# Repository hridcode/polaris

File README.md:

# Polaris

Polaris is a portable cyberdeck for everyday use. It does not use a Raspberry Pi or other SBC, but rather an RP2354B with extra PSRAM! It is meant for having an on-the-go device to use for everyday tasks.

## Features

- RP2354B SoC
- 520KB SRAM + 2MB PSRAM
- 2MB flash memory
- 5x10 thumb-size keyboard
- SD card slot
- USB-C port
- Battery charging with power path (IP2306)
- Audio output through speaker (MAX98357A)
- GPIO access
- Expansion port for apps

## Pictures

|Schematic|PCB|Case|
|---|---|---|
||||

## BOM

|Part|Quantity|Cost|Link|
|---|---|---|---|
|0402 20pF capacitor|2|$0.016|[LCSC](https://www.lcsc.com/product-detail/C1554.html)|
|0402 0.1uF capacitor|13|$0.072|[LCSC](https://www.lcsc.com/product-detail/C1525.html)|
|0402 4.7uF capacitor|3|$0.070|[LCSC](https://www.lcsc.com/product-detail/C23733.html)|
|0402 10uF capacitor|7|$0.181|[LCSC](https://www.lcsc.com/product-detail/C15525.html)|
|0603 22uF capacitor|3|$0.094|[LCSC](https://www.lcsc.com/product-detail/C59461.html)|
|0402 1uH inductor|1|$0.035|[LCSC](https://www.lcsc.com/product-detail/C84468.html)|
|0402 3.3uH inductor|1|$0.076|[LCSC](https://www.lcsc.com/product-detail/C84474.html)|
|0603 2Ω resistor|2|$0.006|[LCSC](https://www.lcsc.com/product-detail/C22977.html)|
|0603 27Ω resistor|2|$0.007|[LCSC](https://www.lcsc.com/product-detail/C25190.html)|
|0402 33Ω resistor|1|$0.008|[LCSC](https://www.lcsc.com/product-detail/C25105.html)|
|0603 220Ω resistor|8|$0.028|[LCSC](https://www.lcsc.com/product-detail/C22962.html)|
|0402 1KΩ resistor|2|$0.008|[LCSC](https://www.lcsc.com/product-detail/C11702.html)|
|0402 4.7KΩ resistor|2|$0.010|[LCSC](https://www.lcsc.com/product-detail/C25905.html)|
|0402 5.1KΩ resistor|2|$0.005|[LCSC](https://www.lcsc.com/product-detail/C25905.html)|
|0402 10KΩ resistor|5|$0.024|[LCSC](https://www.lcsc.com/product-detail/C25905.html)|
|BAW56S quad-diode package|12|$1.778|[LCSC](https://www.lcsc.com/product-detail/C426776.html)|
|USB-C receptacle, 14 pin|1|$0.172|[LCSC](https://www.lcsc.com/product-detail/C165948.html)|
|HDMI-A receptacle|1|$0.245|[LCSC](https://www.lcsc.com/product-detail/C720616.html)|
|microSD card receptacle|1|$0.061|[LCSC](https://www.lcsc.com/product-detail/C7529389.html)|
|3.9x2.9mm tactile switch|48|$1.627|[LCSC](https://www.lcsc.com/product-detail/C557591.html)|
|SPST rocker switch|1|$0.156|[LCSC](https://www.lcsc.com/product-detail/C6917318.html)|
|MAX98357A sound IC|1|$1.328|[LCSC](https://www.lcsc.com/product-detail/C910544.html)|
|Speaker|1|$0.995|[AliExpress](https://www.aliexpress.us/item/3256810283962305.html)|
|IP5306 battery charging IC|1|$0.299|[LCSC](https://www.lcsc.com/product-detail/C181692.html)|
|104050 3.7V 2500mAh LiPo battery|1|$8.790|[AliExpress](https://www.aliexpress.us/item/3256808739822835.html)|
|RP2354B|1|$1.551|[LCSC](https://www.lcsc.com/product-detail/C39843328.html)|
|XC6206P332MR 3.3V power regulator|1|$0.147|[LCSC](https://www.lcsc.com/product-detail/C5446.html)|
|APS1604M-3SQRx-SN 2MB PSRAM|1|$2.586|[LCSC](https://www.lcsc.com/product-detail/C18214056.html)|
|DS3231MZ real-time clock|1|$3.298|[LCSC](https://www.lcsc.com/product-detail/C107410.html)|
|CR1220 battery holder|1|$0.196|[LCSC](https://www.lcsc.com/product-detail/C964723.html)|
|12MHz 20pF crystal oscillator|1|$0.096|[LCSC](https://www.lcsc.com/product-detail/C9002.html)|
|1x5 right-angled pin header|1|$0.075|[LCSC](https://www.lcsc.com/product-detail/C54876734.html)|
|2x7 right-angled pin header|1|$0.328|[LCSC](https://www.lcsc.com/product-detail/C46061748.html)|
|5" 800x480 LCD display|1|$34.990|[Waveshare](https://www.waveshare.com/product/displays/lcd-oled/lcd-oled-1/5inch-hdmi-lcd.htm)|
|Total||$59.358||

## Notes

The firmware is still being developed. There will be more applications once the device is built.

Check `/firmware/src/main.cpp` for libraries/dependencies required to run the firmware.

PNP assembly files are provided if you'd want to get this assembled. The parts list is optimized for JLCPCB's Economic PCB assembly.

Have fun!

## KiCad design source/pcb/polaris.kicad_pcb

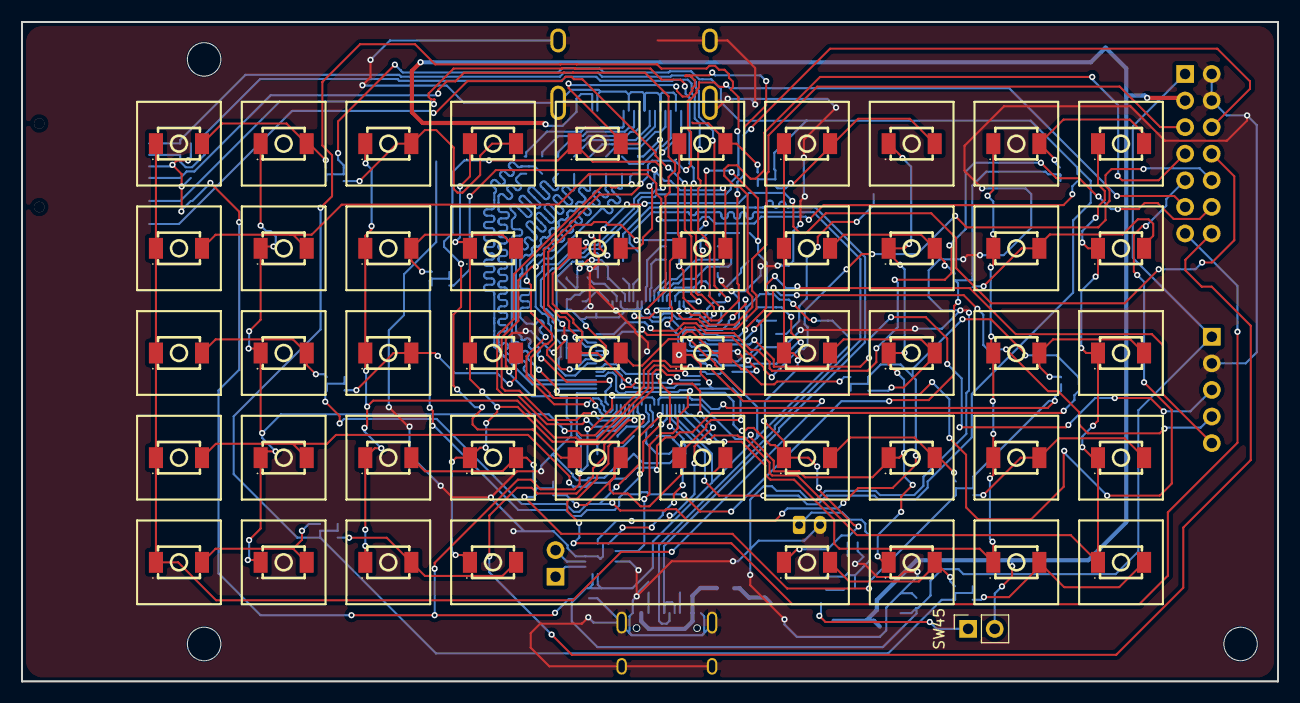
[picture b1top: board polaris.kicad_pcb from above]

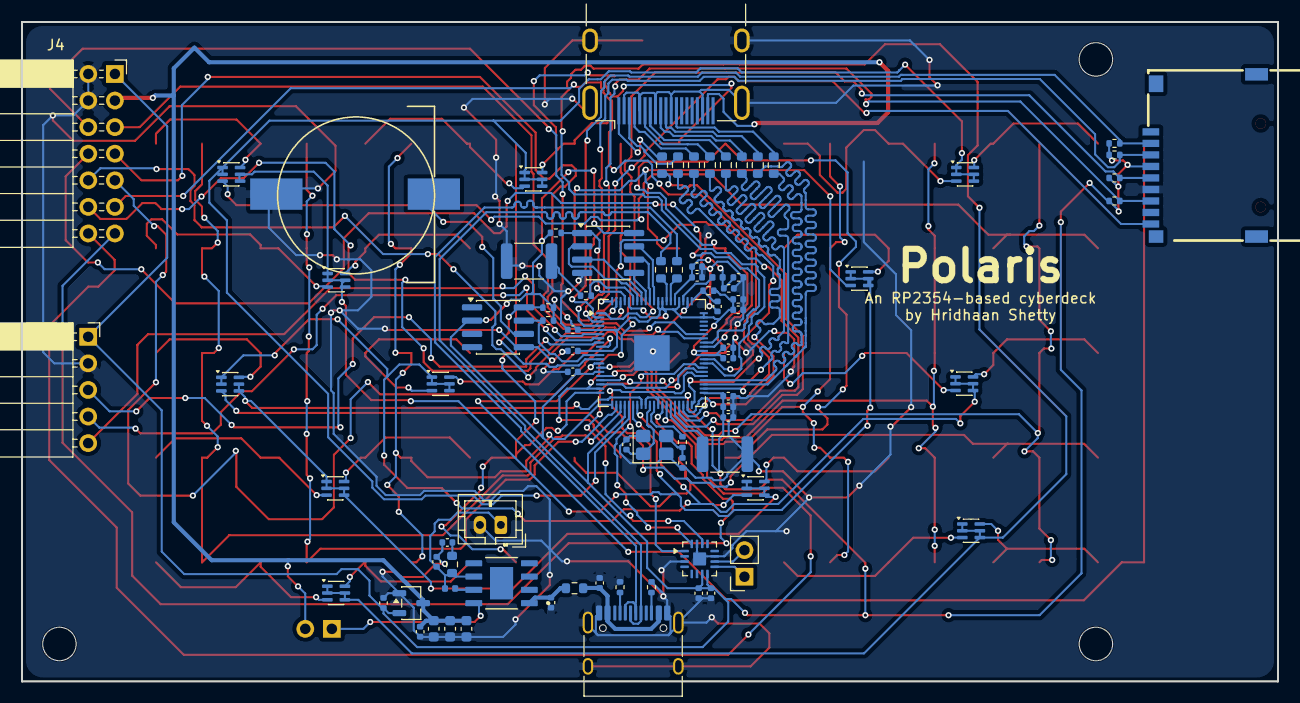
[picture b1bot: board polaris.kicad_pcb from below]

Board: 2 copper layers, 120.0 x 63.0 mm, 135 parts (83 on the bottom side), 111 nets.

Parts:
BT1: Battery_Cell; CR1220_Battery_Holder
C1, C2, C3: 4.7uF; C_0402_1005Metric
C4, C5: 20pF; C_0402_1005Metric
C6, C7, C8, C12, C13, C14, C15, C16, C17, C18, C19, C20, C28: 0.1uF; C_0402_1005Metric
C9, C10, C23, C24, C25, C26, C27: 10uF; C_0402_1005Metric
C11, C21, C22: 22uF; C_0603_1608Metric
D1, D2, D3, D4, D5, D6, D7, D8, D9, D10, D11, D12: BAW56S; SOT-363_SC-70-6
H1, H2, H3: MountingHole; MountingHole_3.2mm_M3
J1: USB_C_Receptacle_USB2.0_14P; USB_C_Receptacle_HRO_TYPE-C-31-M-12
J2: HDMI_A; HDMI_A_Molex_208658-1001_Horizontal
J3: Conn_01x05; PinSocket_1x05_P2.54mm_Horizontal
J4: Conn_02x07_Odd_Even; PinSocket_2x07_P2.54mm_Horizontal
J5: Micro_SD_Card_Det1; TF-SMD_TF-CARD-H1.8
J6: Conn_01x02; JST_PH_B2B-PH-K_1x02_P2.00mm_Vertical
L1: 3.3uH; L_0402_1005Metric
L2: 1uH; L_0402_1005Metric
LS1: Speaker; PinSocket_1x02_P2.54mm_Vertical
R1, R2: 5.1K; R_0402_1005Metric
R3, R4: 27; R_0603_1608Metric
R5: 33; R_0402_1005Metric
R6, R7: 1K; R_0402_1005Metric
R8, R9: 2; R_0603_1608Metric
R10, R11, R12, R13, R14, R15, R16, R17: 220; R_0603_1608Metric
R18, R19: 4.7K; R_0402_1005Metric
R20, R21, R22, R23, R24: 10K; R_0402_1005Metric
SW1, SW2, SW3, SW4, SW5, SW6, SW7, SW8, SW9, SW10, SW11, SW12, SW13, SW14, SW15, SW16, SW17, SW18, SW19, SW20, SW21, SW22, SW23, SW24, SW25, SW26, SW27, SW28, SW29, SW30, SW31, SW32, SW33, SW34, SW35, SW36, SW37, SW38, SW39, SW40, SW41, SW42, SW43, SW44, SW47, SW48, SW49, SW50: SW_Push; SW-SMD_L4.0-W3.0-LS5.0
SW45: SW_SPST; PinSocket_1x02_P2.54mm_Vertical
SW51, SW52: SW_Push; R_1812_4532Metric
U1: MAX98357A; TQFN-16-1EP_3x3mm_P0.5mm_EP1.23x1.23mm
U2: IP5306; eSOP-8
U3: RP2354B; QFN-80-1EP_10x10mm_P0.4mm_EP3.4x3.4mm
U4: XC6206PxxxMR; SOT-23-3
U5: APS1604M-3SQRx-SN; SOIC-8_3.9x4.9mm_P1.27mm
U6: DS3231MZ; SOIC-8_3.9x4.9mm_P1.27mm
Y1: Crystal_GND24; Crystal_SMD_3225-4Pin_3.2x2.5mm

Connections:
+1V1: C2.1, C6.1, C7.1, C8.1, L1.1, U3.65 (VREG_FB)
+3V3: C1.1, C12.1, C13.1, C14.1, C15.1, C16.1, C17.1, C18.1, C19.1, C20.1, C24.1, C27.1, C28.1, J3.1, J4.1, J5.4 (VDD), R5.1, R18.2, R19.1, R20.2, R21.2, R22.2, R23.2, R24.2, U1.7 (VDD), U1.8 (VDD), U3.5 (IOVDD), U3.10 (DVDD), U3.15 (IOVDD), U3.24 (IOVDD), U3.29 (IOVDD), U3.32 (DVDD), U3.41 (IOVDD), U3.50 (IOVDD), U3.51 (DVDD), U3.59 (ADC_AVDD), U3.60 (IOVDD), U3.64 (VREG_VIN), U3.68 (USB_OTP_VDD), U3.69 (QSPI_IOVDD), U3.76 (IOVDD), U4.2 (VO), U5.8 (VDD), U6.2 (VCC)
+5V: C11.1, C21.1, C22.1, C23.1, J2.18 (+5V), J4.3, SW45.2 (B), U4.3 (VI)
ADC0: J4.11, U3.49 (GPIO40/ADC0)
ADC1: J4.6, U3.52 (GPIO41/ADC1)
ADC2: J4.8, U3.53 (GPIO42/ADC2)
ADC3: J4.10, U3.54 (GPIO43/ADC3)
ADC4: J4.12, U3.55 (GPIO44/ADC4)
GND: BT1.2 (-), C1.2, C2.2, C3.2, C4.1, C5.1, C6.2, C7.2, C8.2, C9.2, C10.2, C11.2, C12.2, C13.2, C14.2, C15.2, C16.2, C17.2, C18.2, C19.2, C20.2, C21.2, C22.2, C23.2, C24.2, C25.2, C26.2, C27.2, C28.2, J1.A1 (GND), J1.A12 (GND), J1.B1 (GND), J1.B12 (GND), J1.SH (SHIELD), J2.2 (D2S), J2.5 (D1S), J2.8 (D0S), J2.11 (CKS), J2.17 (GND), J2.SH, J3.2, J4.2, J4.4, J5.6 (VSS), J6.2, R1.2, R2.2, SW51.1, SW52.1, U1.3 (GND), U1.11 (GND), U1.15 (GND), U1.17 (PAD), U3.62 (VREG_PGND), U3.81 (GND), U4.1 (GND), U5.4 (VSS), U6.5 (GND), Y1.2 (G), Y1.4 (G)
GP0: R24.1, U3.77 (GPIO0), U5.1 (~CE)
GP1: J4.5, U3.78 (GPIO1)
GP2: J4.7, U3.79 (GPIO2)
GP3: J5.9 (DET), U3.80 (GPIO3)
GP4: J5.5 (CLK), R20.1, U3.1 (GPIO4)
GP5: J5.2 (DAT3/CD), R21.1, U3.2 (GPIO5)
GP6: J5.7 (DAT0), R22.1, U3.3 (GPIO6)
GP7: J5.3 (CMD), R23.1, U3.4 (GPIO7)
GP8: J3.5, U3.6 (GPIO8)
GP9: J3.4, U3.7 (GPIO9)
GP10: J3.3, U3.8 (GPIO10)
GP11: J4.9, U3.9 (GPIO11)
GP12: R19.2, U3.11 (GPIO12), U6.7 (SDA)
GP13: R18.1, U3.12 (GPIO13), U6.8 (SCL)
GP14: SW1.1, SW11.1, SW21.1, SW31.1, SW41.1, U3.13 (GPIO14)
GP15: SW2.1, SW12.1, SW22.1, SW32.1, SW42.1, U3.14 (GPIO15)
GP16: SW3.1, SW13.1, SW23.1, SW33.1, SW43.1, U3.16 (GPIO16)
GP17: SW4.1, SW14.1, SW24.1, SW34.1, SW44.1, U3.17 (GPIO17)
GP18: SW5.1, SW15.1, SW25.1, SW35.1, U3.18 (GPIO18)
GP19: SW6.1, SW16.1, SW26.1, SW36.1, U3.19 (GPIO19)
GP20: SW7.1, SW17.1, SW27.1, SW37.1, SW47.1, U3.20 (GPIO20)
GP21: SW8.1, SW18.1, SW28.1, SW38.1, SW48.1, U3.21 (GPIO21)
GP22: SW9.1, SW19.1, SW29.1, SW39.1, SW49.1, U3.22 (GPIO22)
GP23: SW10.1, SW20.1, SW30.1, SW40.1, SW50.1, U3.23 (GPIO23)
GP24: D1.1 (K), D1.2 (K), D1.4 (K), D1.5 (K), D2.1 (K), D2.2 (K), D2.4 (K), D2.5 (K), D3.1 (K), D3.2 (K), U3.25 (GPIO24)
GP25: D3.4 (K), D3.5 (K), D4.1 (K), D4.2 (K), D4.4 (K), D4.5 (K), D5.1 (K), D5.2 (K), D5.4 (K), D5.5 (K), U3.26 (GPIO25)
GP26: D6.1 (K), D6.2 (K), D6.4 (K), D6.5 (K), D7.1 (K), D7.2 (K), D7.4 (K), D7.5 (K), D8.1 (K), D8.2 (K), U3.27 (GPIO26)
GP27: D8.4 (K), D8.5 (K), D9.1 (K), D9.2 (K), D9.4 (K), D9.5 (K), D10.1 (K), D10.2 (K), D10.4 (K), D10.5 (K), U3.28 (GPIO27)
GP28: R10.1, U3.36 (GPIO28)
GP29: R11.1, U3.37 (GPIO29)
GP30: R12.1, U3.38 (GPIO30)
GP31: R13.1, U3.39 (GPIO31)
GP32: R14.1, U3.40 (GPIO32)
GP33: R15.1, U3.42 (GPIO33)
GP34: R16.1, U3.43 (GPIO34)
GP35: R17.1, U3.44 (GPIO35)
GP36: U1.1 (DIN), U3.45 (GPIO36)
GP37: U1.14 (LRCLK), U3.46 (GPIO37)
GP38: U1.16 (BCLK), U3.47 (GPIO38)
GP39: D11.1 (K), D11.2 (K), D11.4 (K), D11.5 (K), D12.1 (K), D12.2 (K), D12.4 (K), D12.5 (K), U3.48 (GPIO39)
unnamed: BT1.1 (+), U6.6 (VBAT)
unnamed: C4.2, R7.1, Y1.3
unnamed: C25.1, R9.1
unnamed: D1.6 (A), SW1.2, SW2.2
unnamed: D1.3 (A), SW3.2, SW4.2
unnamed: D2.6 (A), SW5.2, SW6.2
unnamed: D2.3 (A), SW7.2, SW8.2
unnamed: D3.6 (A), SW9.2, SW10.2
unnamed: D3.3 (A), SW11.2, SW12.2
unnamed: D4.6 (A), SW13.2, SW14.2
unnamed: D4.3 (A), SW15.2, SW16.2
unnamed: D5.6 (A), SW17.2, SW18.2
unnamed: D5.3 (A), SW19.2, SW20.2
unnamed: D6.6 (A), SW21.2, SW22.2
unnamed: D6.3 (A), SW23.2, SW24.2
unnamed: D7.6 (A), SW25.2, SW26.2
unnamed: D7.3 (A), SW27.2, SW28.2
unnamed: D8.6 (A), SW29.2, SW30.2
unnamed: D8.3 (A), SW31.2, SW32.2
unnamed: D9.6 (A), SW33.2, SW34.2
unnamed: D9.3 (A), SW35.2, SW36.2
unnamed: D10.6 (A), SW37.2, SW38.2
unnamed: D10.3 (A), SW39.2, SW40.2
unnamed: D11.6 (A), SW41.2, SW42.2
unnamed: D11.3 (A), SW43.2, SW44.2
unnamed: D12.6 (A), SW47.2, SW48.2
unnamed: D12.3 (A), SW49.2, SW50.2
unnamed: J1.A5 (CC1), R1.1
unnamed: J1.B5 (CC2), R2.1
unnamed: J2.10 (CK+), R16.2
unnamed: J2.12 (CK-), R17.2
unnamed: J2.7 (D0+), R14.2
unnamed: J2.9 (D0-), R15.2
unnamed: J2.4 (D1+), R12.2
unnamed: J2.6 (D1-), R13.2
unnamed: J2.1 (D2+), R10.2
unnamed: J2.3 (D2-), R11.2
unnamed: C26.1, J6.1, L2.2, R9.2, U2.6 (BAT)
unnamed: R6.1, SW51.2
unnamed: SW45.1 (A), U2.8 (VOUT)
unnamed: LS1.2, U1.10 (OUTN)
unnamed: LS1.1, U1.9 (OUTP)
unnamed: L2.1, U2.7 (SW)
unnamed: C9.1, R8.2, U2.1 (VIN)
unnamed: SW52.2, U3.35 (RUN)
unnamed: R3.2, U3.66 (USB_DM)
unnamed: R4.2, U3.67 (USB_DP)
unnamed: C5.2, U3.30 (XIN), Y1.1
unnamed: R7.2, U3.31 (XOUT)
unnamed: R6.2, U3.75 (~QSPI_SS)
QSPI_SCLK: U3.71 (QSPI_SCLK), U5.6 (SCLK)
QSPI_SD0: U3.72 (QSPI_SD0), U5.5 (SI/SIO0)
QSPI_SD1: U3.74 (QSPI_SD1), U5.2 (SO/SIO1)
QSPI_SD2: U3.73 (QSPI_SD2), U5.3 (SIO2)
QSPI_SD3: U3.70 (QSPI_SD3), U5.7 (SIO3)
SWCLK: J4.13, U3.33 (SWCLK)
SWDIO: J4.14, U3.34 (SWDIO)
USB D+: J1.A6 (D+), J1.B6 (D+), R4.1
USB D-: J1.A7 (D-), J1.B7 (D-), R3.1
VBUS: C10.1, J1.A4 (VBUS), J1.A9 (VBUS), J1.B4 (VBUS), J1.B9 (VBUS), R8.1
VREG_AVDD: C3.1, R5.2, U3.61 (VREG_AVDD)
VREG_LX: L1.2, U3.63 (VREG_LX)
